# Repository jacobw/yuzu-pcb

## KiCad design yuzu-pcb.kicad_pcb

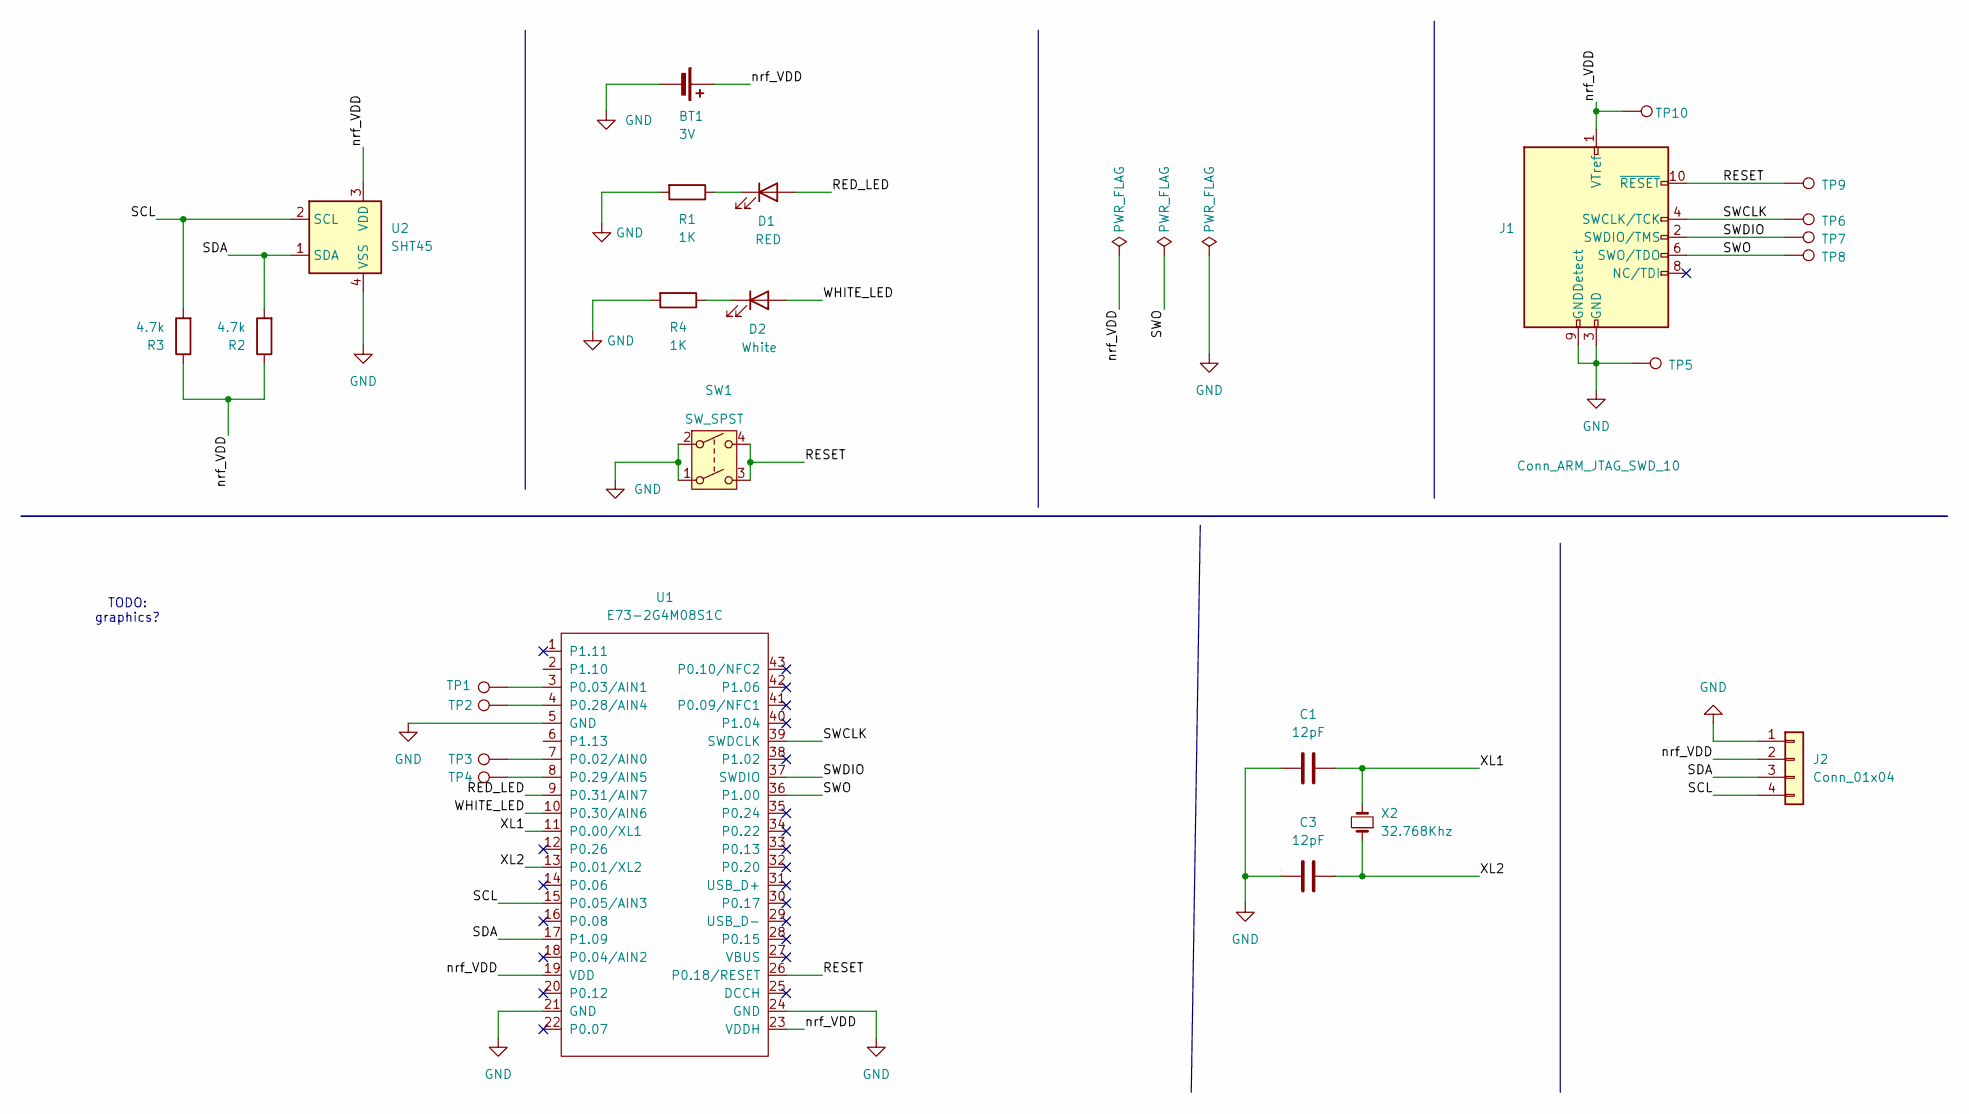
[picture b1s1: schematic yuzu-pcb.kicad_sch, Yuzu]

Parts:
BT1: 3V; BatteryHolder_Keystone_1060_1x2032
C1, C3: 12pF; C_0402_1005Metric
D1: RED; LED_0603_1608Metric
D2: White; LED_0603_1608Metric; LCSC C2290
J1: Conn_ARM_JTAG_SWD_10; FTSH-105-01-L-DV-K
J2: Conn_01x04; JST_SH_BM04B-SRSS-TB_1x04-1MP_P1.00mm_Vertical
R1, R4: 1K; R_0603_1608Metric
R2, R3: 4.7k; R_0603_1608Metric
SW1: SW_SPST; RKB2SJG250SMTRLFS; LCSC C2927788
TP1: A1; TestPoint_THTPad
TP2: A4; TestPoint_THTPad
TP3: A0; TestPoint_THTPad
TP4: A5; TestPoint_THTPad
TP5: GD; TestPoint_THTPad
TP6: CL; TestPoint_THTPad
TP7: IO; TestPoint_THTPad
TP8: WO; TestPoint_THTPad
TP9: RS; TestPoint_THTPad
TP10: VD; TestPoint_THTPad
U1: E73-2G4M08S1C; E73(2G4M08S1C) JLCPCB_2
U2: SHT45; Sensirion_DFN-4_1.5x1.5mm_P0.8mm_SHT4x_NoCentralPad
X2: 32.768Khz; Crystal_SMD_3215-2Pin_3.2x1.5mm; LCSC Q13FC13500004

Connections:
/RED_LED: D1.2 (A), U1.9 (P0.31/AIN7)
/RESET: J1.10 (~RESET), SW1.3, SW1.4, TP9.1, U1.26 (P0.18/RESET)
/SCL: J2.4, R3.2, U1.15 (P0.05/AIN3), U2.2 (SCL)
/SDA: J2.3, R2.2, U1.17 (P1.09), U2.1 (SDA)
/SWCLK: J1.4 (SWCLK/TCK), TP6.1, U1.39 (SWDCLK)
/SWDIO: J1.2 (SWDIO/TMS), TP7.1, U1.37 (SWDIO)
/SWO: J1.6 (SWO/TDO), TP8.1, U1.36 (P1.00)
/WHITE_LED: D2.2 (A), U1.10 (P0.30/AIN6)
/XL1: C1.1, U1.11 (P0.00/XL1), X2.2
/XL2: C3.1, U1.13 (P0.01/XL2), X2.1
/nrf_VDD: BT1.1 (+), J1.1 (VTref), J2.2, R2.1, R3.1, TP10.1, U1.19 (VDD), U1.23 (VDDH), U2.3 (VDD)
GND: BT1.2 (-), C1.2, C3.2, J1.3 (GND), J1.5 (GND), J1.9 (GNDDetect), J2.1, R1.2, R4.2, SW1.1, SW1.2, TP5.1, U1.5 (GND), U1.21 (GND), U1.24 (GND), U2.4 (VSS)
unnamed: D1.1 (K), R1.1
unnamed: D2.1 (K), R4.1
unnamed: TP3.1, U1.7 (P0.02/AIN0)
unnamed: TP1.1, U1.3 (P0.03/AIN1)
unnamed: TP2.1, U1.4 (P0.28/AIN4)
unnamed: TP4.1, U1.8 (P0.29/AIN5)

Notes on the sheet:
TODO: graphics?

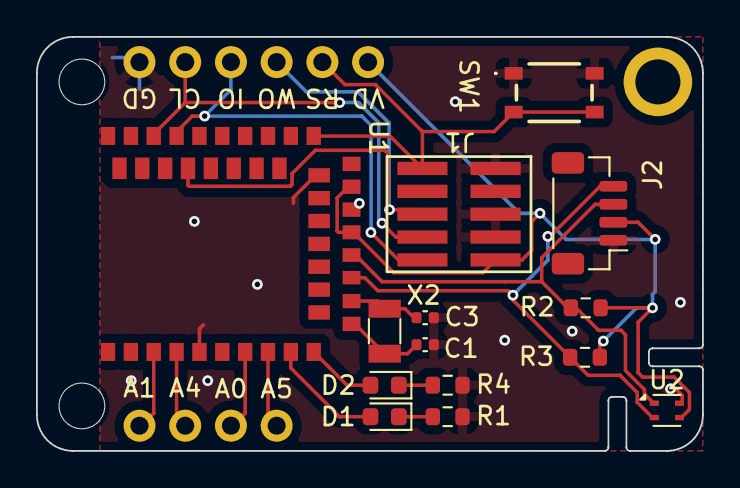
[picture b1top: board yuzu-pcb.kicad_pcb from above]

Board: 2 copper layers, 37.0 x 23.0 mm, 25 parts (1 on the bottom side), 18 nets.

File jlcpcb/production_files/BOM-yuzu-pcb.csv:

Comment,Designator,Footprint,LCSC
White,D2,LED_0603_1608Metric,C2290
SW_SPST,SW1,RKB2SJG250SMTRLFS,C2927788
4.7k,R2,R_0603_1608Metric,
32.768Khz,X2,Crystal_SMD_3215-2Pin_3.2x1.5mm,
12pF,C3,C_0402_1005Metric,
4.7k,R3,R_0603_1608Metric,
1K,R1,R_0603_1608Metric,
SHT45,U2,Sensirion_DFN-4_1.5x1.5mm_P0.8mm_SHT4x_NoCentralPad,
12pF,C1,C_0402_1005Metric,
E73-2G4M08S1C,U1,E73(2G4M08S1C) JLCPCB_2,
RED,D1,LED_0603_1608Metric,
3V,BT1,BatteryHolder_Keystone_1060_1x2032,
1K,R4,R_0603_1608Metric,

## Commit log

2024-04-27 Add files
2024-05-03 Update project
2024-05-17 Updated schematic and pcb
2024-05-18 Minor updates
2024-05-24 More updates
2024-06-03 Add pdf of schematic for v1.0.0
2024-08-13 Sent for production
2024-08-13 Update pdf
